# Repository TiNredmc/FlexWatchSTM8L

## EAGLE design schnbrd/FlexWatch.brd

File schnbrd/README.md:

# This is the Schematic and board for the FPC breakout and controller board.

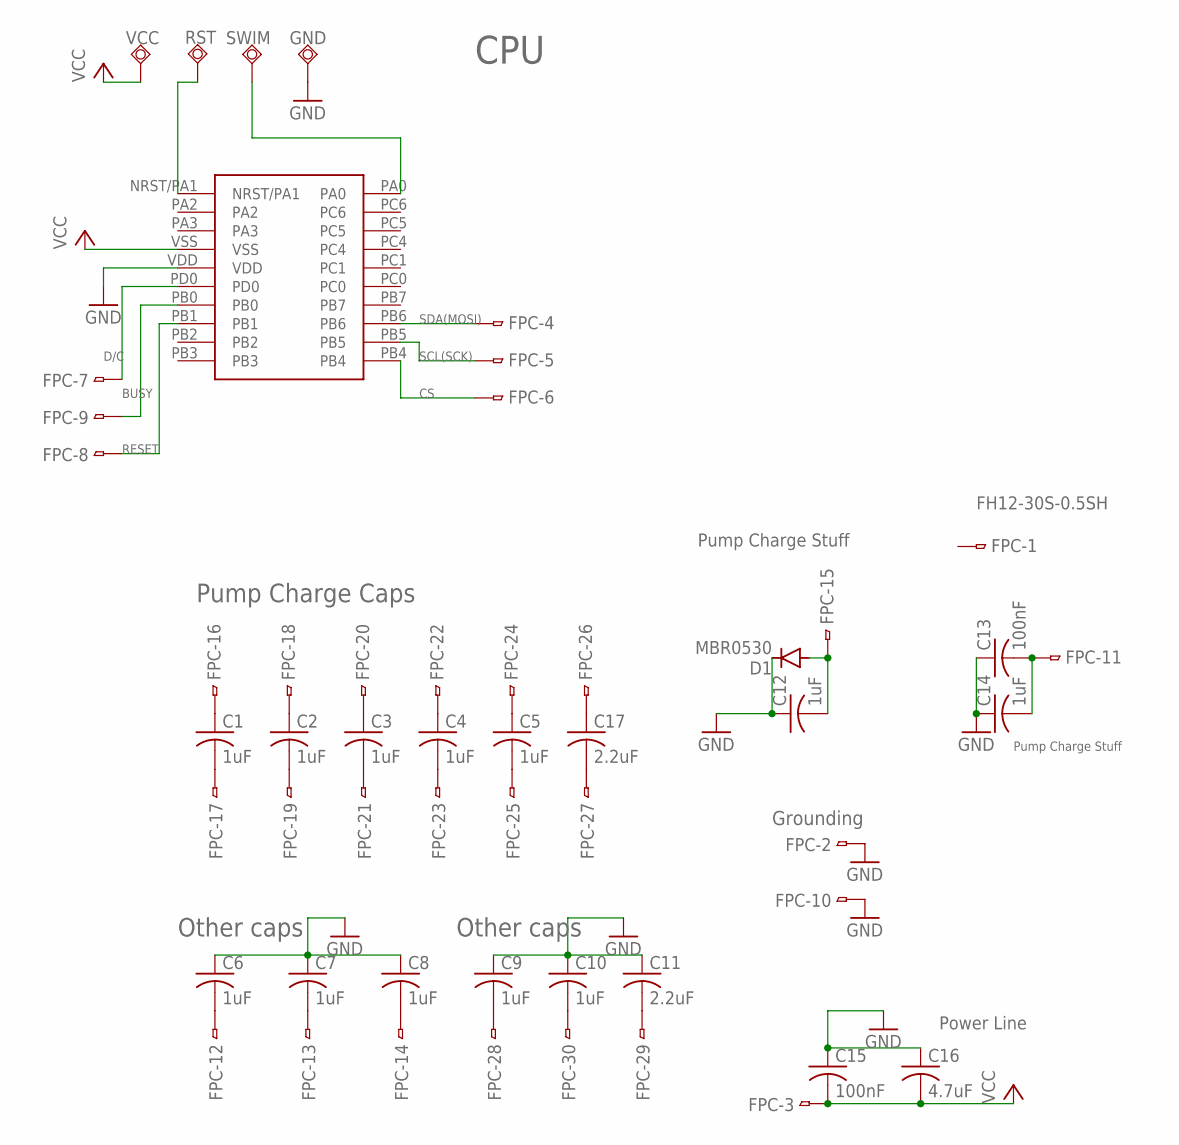
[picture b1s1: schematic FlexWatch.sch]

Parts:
C1, C2, C3, C4, C5, C6, C7, C8, C9, C10, C12, C14: 1uF; C0805
C11, C17: 2.2uF; C1206
C13, C15: 100nF; C0805
C16: 4.7uF; C0805
D1: MBR0530; SOD-123_MINI-SMA
FPC: FH12-30S-0.5SH
GND: TPSQTP18SQ; TP18SQ
RST: TPSQTP18SQ; TP18SQ
SWIM: TPSQTP18SQ; TP18SQ
U$1: STM8L151F3; UFQFPN-20
VCC: TPSQTP18SQ; TP18SQ

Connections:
BUSY: FPC.9, U$1.PB0
CS: FPC.6, U$1.PB4
D/C: FPC.7, U$1.PD0
GND: C6.1, C7.1, C8.1, C9.1, C10.1, C11.1, C12.1, C13.1, C14.1, C15.1, C16.1, D1.C, FPC.2, FPC.10, GND.TP, U$1.VDD
unnamed: C1.1, FPC.16
unnamed: C1.2, FPC.17
unnamed: C2.1, FPC.18
unnamed: C2.2, FPC.19
unnamed: C3.1, FPC.20
unnamed: C3.2, FPC.21
unnamed: C4.1, FPC.22
unnamed: C4.2, FPC.23
unnamed: C5.1, FPC.24
unnamed: C5.2, FPC.25
unnamed: C6.2, FPC.12
unnamed: C7.2, FPC.13
unnamed: C8.2, FPC.14
unnamed: C12.2, D1.A, FPC.15
unnamed: C11.2, FPC.29
unnamed: C9.2, FPC.28
unnamed: C10.2, FPC.30
unnamed: C13.2, C14.2, FPC.11
unnamed: C17.1, FPC.26
unnamed: C17.2, FPC.27
unnamed: RST.TP, U$1.NRST/PA1
unnamed: SWIM.TP, U$1.PA0
RESET: FPC.8, U$1.PB1
SCL(SCK): FPC.5, U$1.PB5
SDA(MOSI): FPC.4, U$1.PB6
VCC: C15.2, C16.2, FPC.3, U$1.VSS, VCC.TP

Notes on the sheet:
Pump Charge Caps
Other caps
Grounding
Pump Charge Stuff
Power Line
CPU

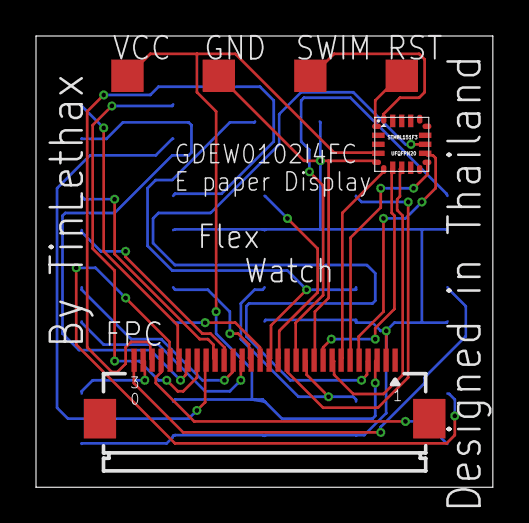
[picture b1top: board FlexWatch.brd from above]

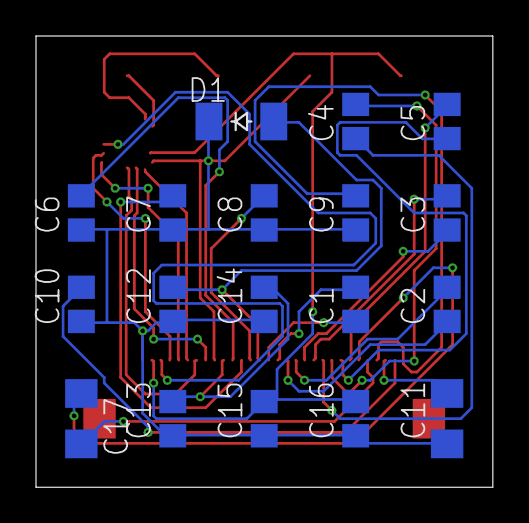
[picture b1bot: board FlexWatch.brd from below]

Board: 2 copper layers, 25.4 x 25.1 mm, 24 parts (18 on the bottom side), 30 nets.

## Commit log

2019-11-04 Upload the board adapter.
2019-11-04 Rename board.brd to FPCboard.brd
2019-11-04 Rename board.sch to FPCboard.sch
2019-11-04 the controller board
